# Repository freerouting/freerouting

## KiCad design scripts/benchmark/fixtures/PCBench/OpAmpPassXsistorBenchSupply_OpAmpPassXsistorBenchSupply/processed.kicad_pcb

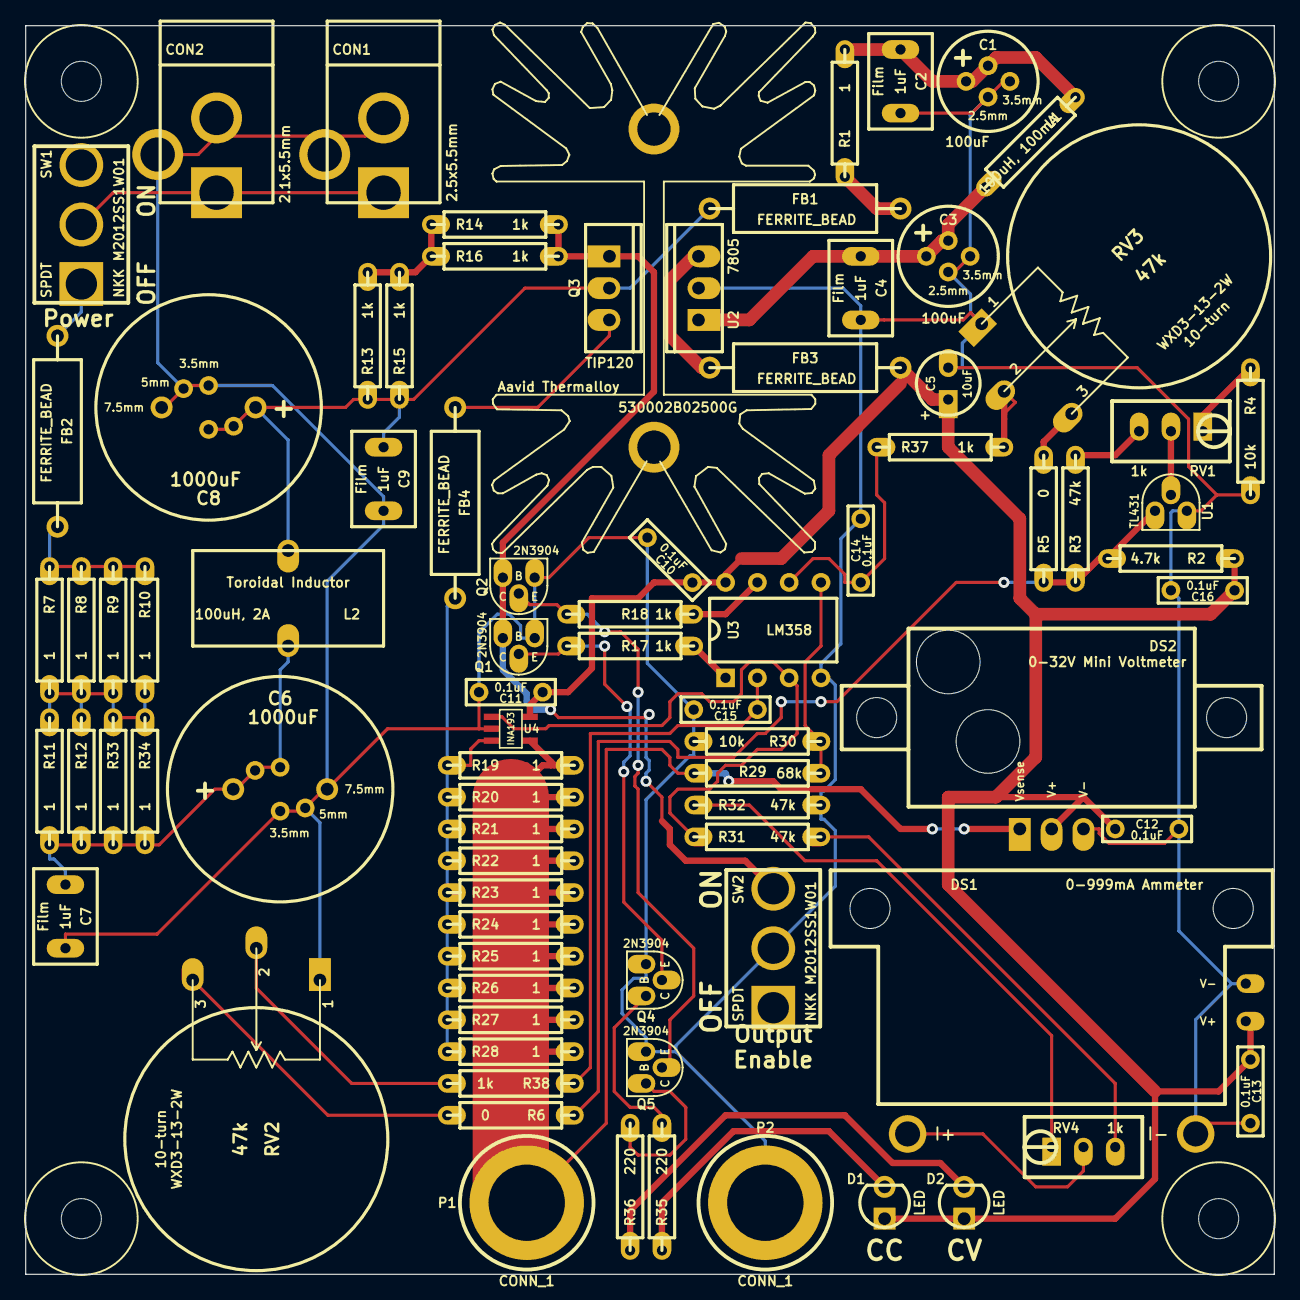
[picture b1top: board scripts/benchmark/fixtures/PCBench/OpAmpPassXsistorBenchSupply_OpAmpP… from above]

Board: 2 copper layers, 99.7 x 99.7 mm, 88 parts (0 on the bottom side), 40 nets.

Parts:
C1, C3: 100uF; MedCap
C2, C4, C7, C9: 1uF; BOXCAP_02_03_02_059C
C5: 10uF; ELCAP_10_20_V_059Bo
C6, C8: 1000uF; BigCap
C10, C11, C12, C13, C14, C15, C16: 0.1uF; CERCAP_2_059A
CON1: 2.5x5.5mm; BARREL_JACK_25x55
CON2: 2.1x5.5mm; BARREL_JACK_21x55
D1, D2: LED; LED_3MM_069A
DS1: AMMETER_V; EBAY_AMMETER
DS2: VOLTMETER; DVM036A
FB1, FB2, FB3, FB4: FERRITE_BEAD; FERRITE_AXIAL_06_069A
H1, H2, H3, H4: HOLE; hole_M3_NPTH
H***: 530002B02500G
L1: 100uH, 100mA; R_AXIAL_0W25_059Bi
L2: 100uH, 2A; Toroid_V_06_03_069Bi
P1, P2: CONN_1; Banana_A
Q1, Q2, Q4, Q5: 2N3904; TO-92_Q_EBC
Q3: TIP120; TO-220_V_069B
R1, R7, R8, R9, R10, R11, R12, R19, R20, R21, R22, R23, R24, R25, R26, R27, R28, R33, R34: 1; R_AXIAL_0W25_059Bi
R2: 4.7k; R_AXIAL_0W25_059Bi
R3, R31, R32: 47k; R_AXIAL_0W25_059Bi
R4, R30: 10k; R_AXIAL_0W25_059Bi
R5, R6: 0; R_AXIAL_0W25_059Bi
R13, R14, R15, R16, R17, R18, R37, R38: 1k; R_AXIAL_0W25_059Bi
R29: 68k; R_AXIAL_0W25_059Bi
R35, R36: 220; R_AXIAL_0W25_059Bi
RV1, RV4: 1k; 3296W
RV2, RV3: 47k; WXD3-13-2W_A
SW1, SW2: SPDT; M2012SS1W01
U1: TL431; TO-92_U_059Bo
U2: 7805; TO-220_V_069B
U3: LM358; DIP8_059A
U4: INA193; SOT23-5

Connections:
/Base: Q1.3, Q2.3, Q3.1, R14.2, R16.2, SW2.3
GND: C1.2, C2.2, C3.2, C4.2, C5.2, C6.2, C7.2, C8.2, C9.2, C10.2, C11.2, C12.2, C13.2, C14.2, C15.2, C16.2, CON1.2, CON1.3, CON2.2, CON2.3, DS1.2, DS1.4, DS2.3, P2.1, Q1.1, Q2.1, Q4.1, Q5.1, R4.2, R30.2, R32.2, RV2.1, RV3.1, SW2.2, U1.3, U2.2, U3.4, U4.2
Icontrol: C15.1, R38.1, U3.2
Isense: R31.1, U3.3, U4.1
unnamed: R5.2, RV3.3
unnamed: R32.1, RV4.1
unnamed: R31.2, RV4.3
unnamed: DS1.1, RV4.2
unnamed: R6.2, RV2.3
unnamed: CON1.1, CON2.1, SW1.2
unnamed: C6.1, C7.1, L2.1, R11.2, R12.2, R33.2, R34.2
unnamed: R7.2, R8.2, R9.2, R10.2, R11.1, R12.1, R33.1, R34.1
unnamed: RV1.2, U1.2
unnamed: FB3.1, U2.3
unnamed: FB4.1, Q3.3
unnamed: FB2.1, SW1.1
unnamed: FB1.2, R1.1
unnamed: R18.2, U3.7
unnamed: R4.1, RV1.1
unnamed: R3.2, RV1.3
unnamed: R17.2, U3.1
unnamed: Q2.2, Q5.2, R18.1
unnamed: Q5.3, R36.2
unnamed: D2.2, R36.1
unnamed: Q4.3, R35.2
unnamed: D1.2, R35.1
unnamed: Q1.2, Q4.2, R17.1
unnamed: R37.2, RV3.2
unnamed: R38.2, RV2.2
unnamed: R13.2, R14.1, R15.2, R16.1
unnamed: C3.1, C4.1, L1.2, U2.1
unnamed: FB2.2, R7.1, R8.1, R9.1, R10.1
unnamed: C1.1, C2.1, L1.1, R1.2
Shunt+: FB4.2, R19.1, R20.1, R21.1, R22.1, R23.1, R24.1, R25.1, R26.1, R27.1, R28.1, U4.3
Shunt-: DS2.1, P1.1, R19.2, R20.2, R21.2, R22.2, R23.2, R24.2, R25.2, R26.2, R27.2, R28.2, R29.1, U4.4
VREF: R2.2, R3.1, R5.1, R6.1, U1.1
Vcc_filt: C8.1, C9.1, FB1.1, L2.2, Q3.2, R13.1, R15.1
Vcc_reg: C5.1, C10.1, C11.1, C12.1, C13.1, C16.1, D1.1, D2.1, DS1.3, DS2.2, FB3.2, R2.1, U3.8, U4.5
Vcontrol: C14.1, R37.1, U3.6
Vsense: R29.2, R30.1, U3.5

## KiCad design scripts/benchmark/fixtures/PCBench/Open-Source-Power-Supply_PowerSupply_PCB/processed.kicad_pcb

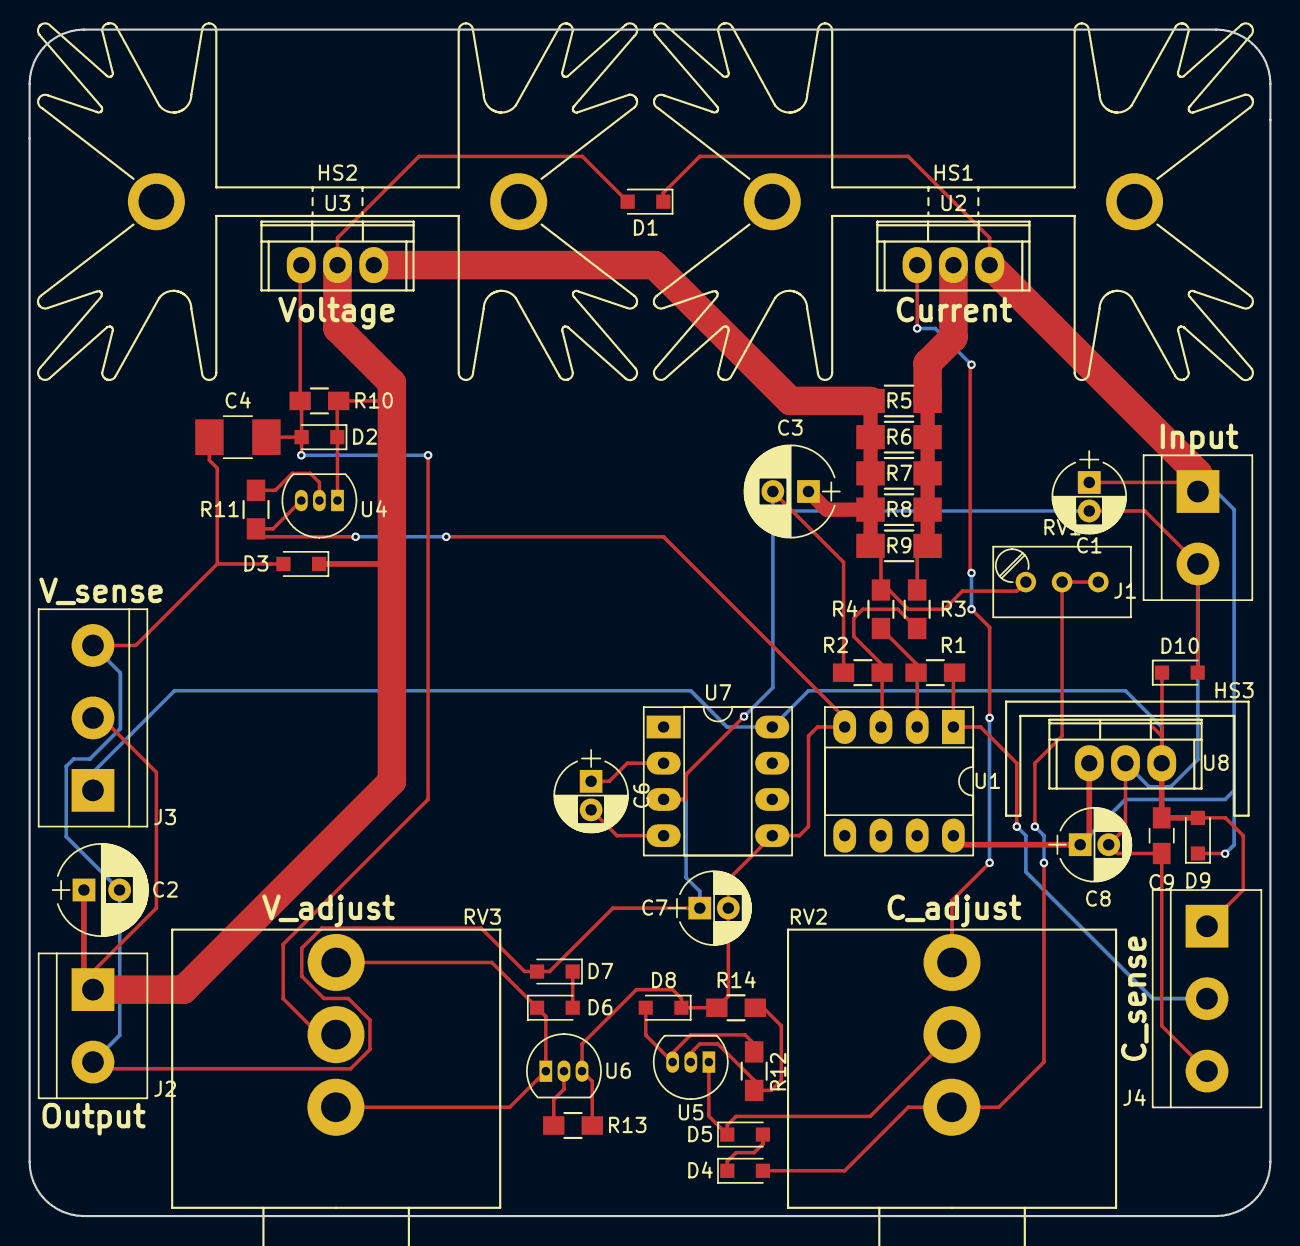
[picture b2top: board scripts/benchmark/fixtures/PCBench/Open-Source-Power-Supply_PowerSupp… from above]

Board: 2 copper layers, 87.0 x 83.2 mm, 50 parts (0 on the bottom side), 23 nets.

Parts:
C1, C6, C7, C8: 10u; CP_Radial_D5.0mm_P2.00mm
C2: 47uF electro; CP_Radial_D6.3mm_P2.50mm
C3: 47u; CP_Radial_D6.3mm_P2.50mm
C4: 4.7u; C_1210_HandSoldering
C9: 0.1u; C_0805_HandSoldering
D1, D2, D3, D9, D10: 1N5819; D_SOD-323_HandSoldering
D4, D5, D6, D7, D8: 1N4448; D_SOD-323_HandSoldering
HS1, HS2: Heatsink; Heatsink_Fischer_SK129-STS_42x25mm_2xDrill2.5mm
HS3: Heatsink; TO220-Small-16mmx8mm
J1: Input Voltage; bornier2
J2: Output Voltage; bornier2
J3: Voltage Meter; bornier3
J4: Current Meter; bornier3
R1, R2: 50k; R_0805_HandSoldering
R3, R4: 10k; R_0805_HandSoldering
R5, R6, R7, R8, R9: 10; R_1206_HandSoldering
R10: 1k; R_0805_HandSoldering
R11, R13: 15; R_0805_HandSoldering
R12: 33; R_0805_HandSoldering
R14: 330; R_0805_HandSoldering
RV1: 100 (multiturn); Potentiometer_Trimmer_Bourns_3296W
RV2, RV3: 10k; Potentiometer-3596S-10k-Pot
U1: LT1013; DIP-8_W7.62mm_Socket_LongPads
U2: LT1086; TO-220
U3: LM1117-ADJ; TO-220
U4, U5, U6: LM334Z; TO-92_Inline_Narrow_Oval
U7: ICL7660; DIP-8_W7.62mm_Socket_LongPads
U8: LM7812CT; TO-220

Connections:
+12V: C9.1, D9.2, D10.1, J3.1, J4.1, U7.8, U8.3
+16V: C1.1, C8.1, D1.1, D9.1, J1.1, U1.8, U2.3, U8.1
-12V: C7.2, D8.1, R11.2, R13.2, R14.2, U1.4, U4.3, U6.3, U7.5
CurrentMeter: J4.2, R1.1, U1.1
GND: C1.2, C2.2, C3.2, C4.2, C7.1, C8.2, C9.2, D3.2, D7.2, D10.2, J1.2, J2.2, J3.3, J4.3, R2.2, U7.3, U8.2
unnamed: C3.1, R4.2, R5.1, R6.1, R7.1, R8.1, R9.1, RV1.1, U3.3
unnamed: C4.1, D2.2, R10.2, RV3.1, U3.1
unnamed: C6.1, U7.2
unnamed: C6.2, U7.4
unnamed: D4.1, D5.2
unnamed: D4.2, RV1.2, RV1.3, RV2.3
unnamed: D5.1, RV2.1, U5.1
unnamed: D6.1, RV3.2, RV3.3, U6.1
unnamed: D6.2, D7.1
unnamed: D8.2, R12.2, U5.3
unnamed: R1.2, R4.1, U1.2
unnamed: R2.1, R3.1, U1.3
unnamed: R3.2, R5.2, R6.2, R7.2, R8.2, R9.2, U2.2
unnamed: R11.1, U4.2
unnamed: R12.1, R14.1, U5.2
unnamed: R13.1, U6.2
unnamed: RV2.2, U2.1
VoltageMeter: C2.1, D1.2, D2.1, D3.1, J2.1, J3.2, R10.1, U3.2, U4.1
